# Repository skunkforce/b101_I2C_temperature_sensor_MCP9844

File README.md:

# edgy_board number b101
This design is part of the [edgy board project](https://github.com/skunkforce/edgy_boards). It provides the functionality of the digital temperature sensor MCP9844 via interfaces I2C. 

# getting started
This repository uses submodules. After cloning use the command 

```$ git submodule update --init --recursive```

to pull the submodules before opening the project with kicad. 

# Tests
Tests can be found in [TESTS.md](TESTS.md)

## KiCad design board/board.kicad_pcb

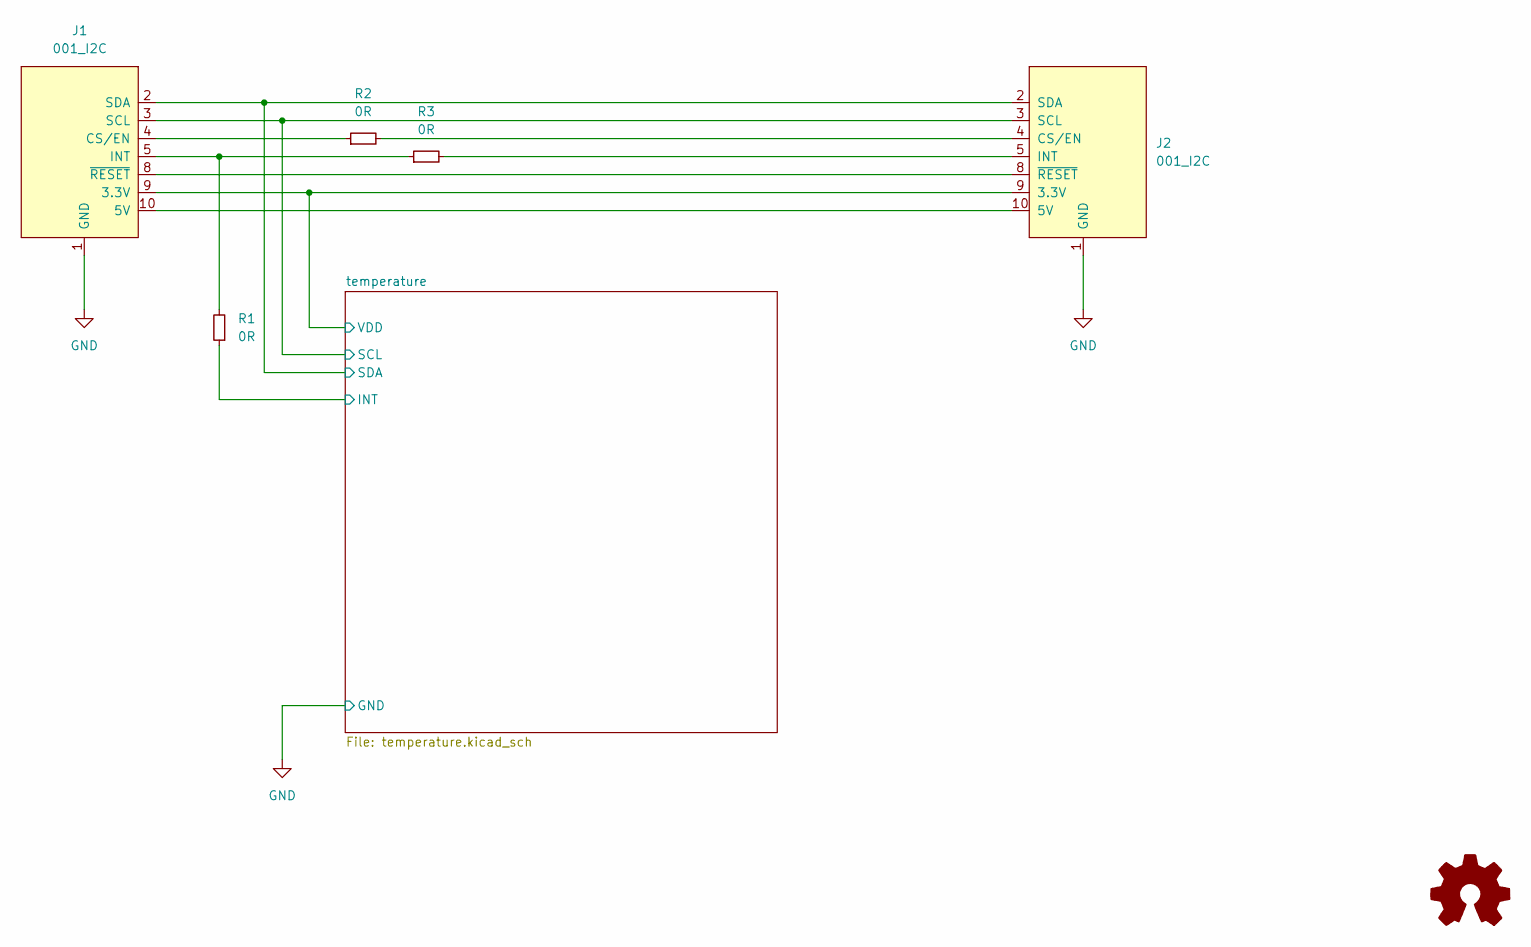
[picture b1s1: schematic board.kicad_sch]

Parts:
J1: 001_I2C; on_edge_2x05_device
J2: 001_I2C; on_edge_2x05_host
LOGO1: Logo_Open_Hardware_Small; OSHW-Symbol_6.7x6mm_SilkScreen
R1, R2, R3: 0R; R_0603_1608Metric

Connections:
/temperature/INT: R1.1; also elsewhere on the board
/temperature/SCL: J1.3 (SCL), J2.3 (SCL); also elsewhere on the board
/temperature/SDA: J1.2 (SDA), J2.2 (SDA); also elsewhere on the board
/temperature/VDD: J1.9 (3.3V), J2.9 (3.3V); also elsewhere on the board
GND: J1.1 (GND), J2.1 (GND); also elsewhere on the board
unnamed: J1.4 (CS/EN), R2.1
unnamed: J1.5 (INT), R1.2, R3.1
unnamed: J1.8 (~RESET), J2.8 (~RESET)
unnamed: J1.10 (5V), J2.10 (5V)
unnamed: J2.4 (CS/EN), R2.2
unnamed: J2.5 (INT), R3.2

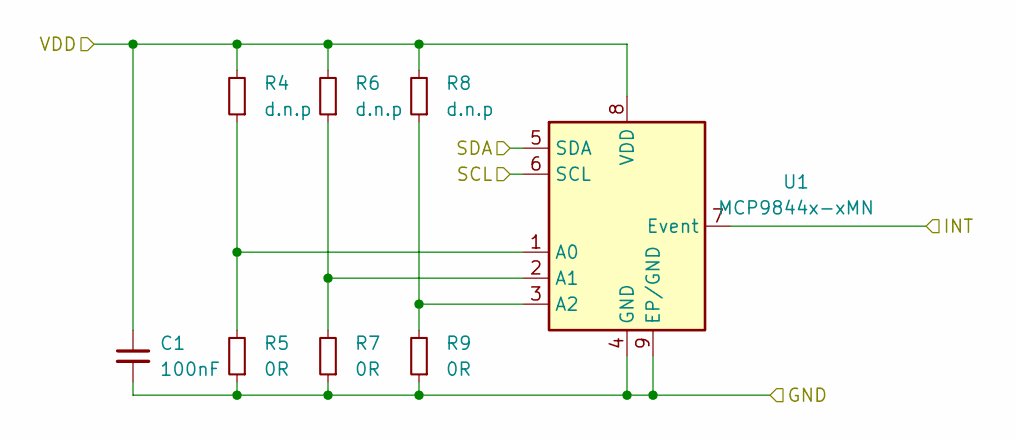
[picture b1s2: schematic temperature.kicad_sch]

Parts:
C1: 100nF; C_0603_1608Metric
R4, R6, R8: d.n.p; R_0603_1608Metric
R5, R7, R9: 0R; R_0603_1608Metric
U1: MCP9844x-xMN; DFN-8-1EP_3x2mm_P0.5mm_EP1.36x1.46mm

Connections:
/temperature/INT: U1.7 (Event); also elsewhere on the board
/temperature/SCL: U1.6 (SCL); also elsewhere on the board
/temperature/SDA: U1.5 (SDA); also elsewhere on the board
/temperature/VDD: C1.1, R4.2, R6.2, R8.2, U1.8 (VDD); also elsewhere on the board
GND: C1.2, R5.1, R7.1, R9.1, U1.4 (GND), U1.9 (EP/GND); also elsewhere on the board
unnamed: R4.1, R5.2, U1.1 (A0)
unnamed: R6.1, R7.2, U1.2 (A1)
unnamed: R8.1, R9.2, U1.3 (A2)

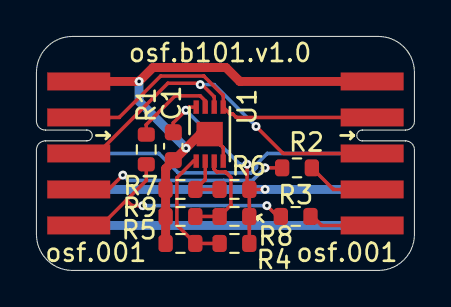
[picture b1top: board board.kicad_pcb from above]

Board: 2 copper layers, 21.0 x 13.0 mm, 14 parts (1 on the bottom side), 14 nets.

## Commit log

2023-02-27 initial README
2023-02-27 initial TESTS
2023-02-27 initial
2023-03-08 added board name on silkscreen
